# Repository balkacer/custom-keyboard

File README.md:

# Orange Moon Keyboard

This is a custom keyboard for the streamer [blodiemoon](https://www.twitch.tv/blodiemoon).

## Design

## Legends

## Plate Layout

## External links

- [Twitch](https://www.twitch.tv/blodiemoon)
- [Keyboard Layout Editor](http://www.keyboard-layout-editor.com/)
- [Auto Hotkey](https://www.autohotkey.com/)

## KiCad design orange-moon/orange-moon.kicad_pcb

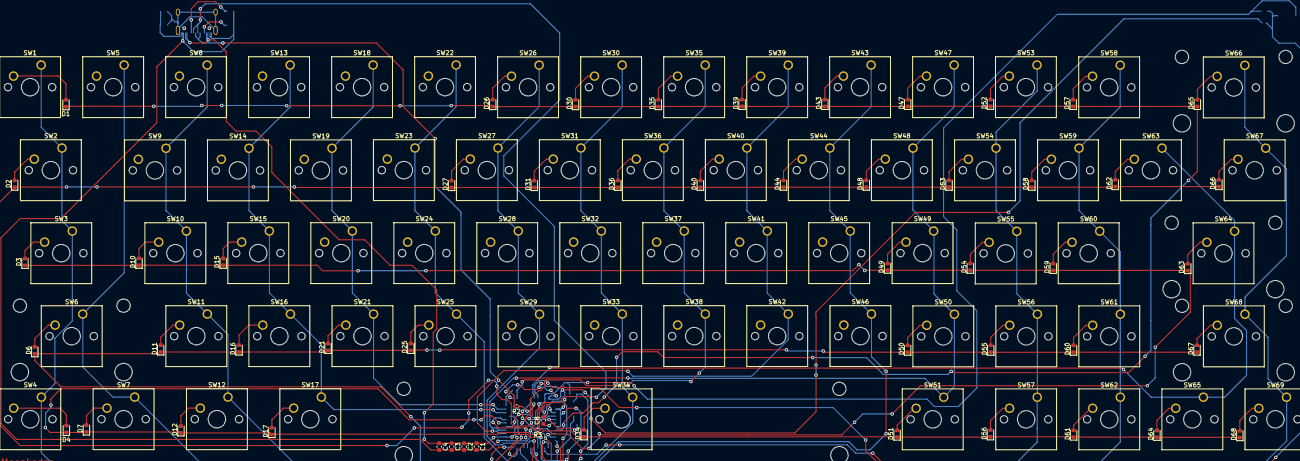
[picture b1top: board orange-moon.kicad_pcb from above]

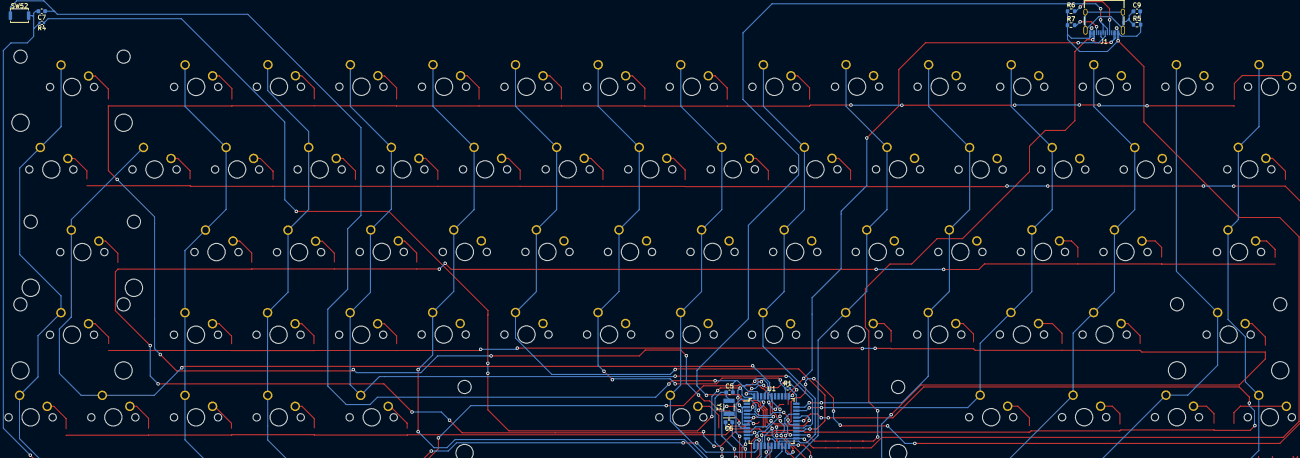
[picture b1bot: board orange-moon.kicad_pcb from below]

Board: 2 copper layers, 135 parts (13 on the bottom side), 82 nets.

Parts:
C1: 10u; C_0603_1608Metric
C2, C8: 1u; C_0603_1608Metric
C3, C4: 100u; C_0603_1608Metric
C5, C6: 22p; C_0603_1608Metric
C7, C9: 100n; C_0603_1608Metric
D1, D2, D3, D4, D6, D7, D10, D11, D12, D15, D16, D17, D21, D25, D26, D27, D30, D31, D34, D35, D36, D39, D40, D43, D44, D47, D48, D49, D50, D51, D52, D53, D54, D55, D56, D57, D58, D59, D60, D61, D62, D63, D64, D65, D66, D67, D68: D_Small; D_0603_1608Metric
J1: USB_C_Receptacle; USB_C_Receptacle_XKB_U262-16XN-4BVC11
R1, R4: 10k; R_0402_1005Metric
R2, R3: 22; R_0402_1005Metric
R5: 1M; R_0603_1608Metric
R6, R7: 5.1k; R_0603_1608Metric
SW1, SW4, SW5, SW8, SW9, SW10, SW11, SW12, SW13, SW14, SW15, SW16, SW18, SW19, SW20, SW21, SW22, SW23, SW24, SW25, SW26, SW27, SW28, SW29, SW30, SW31, SW32, SW33, SW35, SW36, SW37, SW38, SW39, SW40, SW41, SW42, SW43, SW44, SW45, SW46, SW47, SW48, SW49, SW50, SW53, SW54, SW55, SW56, SW57, SW58, SW59, SW60, SW61, SW62, SW63, SW65, SW69: Mechanical_Switch; SW_Cherry_MX_1.00u_PCB
SW2, SW67: Mechanical_Switch; SW_Cherry_MX_1.50u_PCB
SW3: Mechanical_Switch; SW_Cherry_MX_1.75u_PCB
SW6, SW66, SW68: Mechanical_Switch; SW_Cherry_MX_2.00u_PCB
SW7, SW17, SW51: Mechanical_Switch; SW_Cherry_MX_1.25u_PCB
SW34: Mechanical_Switch; SW_Cherry_MX_6.25u_PCB
SW52: SW_Push; SW_Push_SPST_NO_Alps_SKRK
SW64: Mechanical_Switch; SW_Cherry_MX_2.25u_PCB
U1: ATmega32U4-A; TQFP-44_10x10mm_P0.8mm
Y1: 16MHz; Resonator_SMD_Murata_CDSCB-2Pin_4.5x2.0mm

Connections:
+5V: C1.1, C2.1, C3.1, C4.1, J1.A4 (VBUS), J1.A9 (VBUS), J1.B4 (VBUS), J1.B9 (VBUS), R4.1, U1.2 (UVCC), U1.7 (VBUS), U1.14 (VCC), U1.24 (AVCC), U1.34 (VCC), U1.44 (AVCC)
COL1: SW1.1, SW2.1, SW3.1, SW4.1, U1.29 (PB5)
COL2: SW5.1, SW6.1, SW7.1, U1.30 (PB6)
COL3: SW8.1, SW9.1, SW10.1, SW11.1, SW12.1, U1.12 (PB7)
COL4: SW13.1, SW14.1, SW15.1, SW16.1, SW17.1, U1.31 (PC6)
COL5: SW18.1, SW19.1, SW20.1, SW21.1, U1.32 (PC7)
COL6: SW22.1, SW23.1, SW24.1, SW25.1, U1.18 (PD0)
COL7: SW26.1, SW27.1, SW28.1, SW29.1, U1.19 (PD1)
COL8: SW30.1, SW31.1, SW32.1, SW33.1, SW34.1, U1.20 (PD2)
COL9: SW35.1, SW36.1, SW37.1, SW38.1, U1.21 (PD3)
COL10: SW39.1, SW40.1, SW41.1, SW42.1, U1.25 (PD4)
COL11: SW43.1, SW44.1, SW45.1, SW46.1, U1.22 (PD5)
COL12: SW47.1, SW48.1, SW49.1, SW50.1, SW51.1, U1.26 (PD6)
COL13: SW53.1, SW54.1, SW55.1, SW56.1, SW57.1, U1.27 (PD7)
COL14: SW58.1, SW59.1, SW60.1, SW61.1, SW62.1, U1.41 (PF0)
COL15: SW63.1, SW64.1, SW65.1, U1.40 (PF1)
COL16: SW66.1, SW67.1, SW68.1, SW69.1, U1.39 (PF4)
GND: C1.2, C2.2, C3.2, C4.2, C5.2, C6.2, C7.1, C8.2, C9.2, J1.A1 (GND), J1.A12 (GND), J1.B1 (GND), J1.B12 (GND), R1.1, R5.2, R6.1, R7.1, SW52.1, U1.5 (UGND), U1.15 (GND), U1.23 (GND), U1.35 (GND), U1.43 (GND)
unnamed: C5.1, U1.17 (XTAL1), Y1.2
unnamed: C6.1, U1.16 (XTAL2), Y1.1
unnamed: C8.1, U1.6 (UCAP)
unnamed: C9.1, J1.S1 (SHIELD), R5.1
unnamed: D1.2 (A), SW1.2
unnamed: D2.2 (A), SW2.2
unnamed: D3.2 (A), SW3.2
unnamed: D4.2 (A), SW4.2
unnamed: D6.2 (A), SW6.2
unnamed: D7.2 (A), SW7.2
unnamed: D10.2 (A), SW10.2
unnamed: D11.2 (A), SW11.2
unnamed: D12.2 (A), SW12.2
unnamed: D15.2 (A), SW15.2
unnamed: D16.2 (A), SW16.2
unnamed: D21.2 (A), SW21.2
unnamed: D25.2 (A), SW25.2
unnamed: D27.2 (A), SW27.2
unnamed: D31.2 (A), SW31.2
unnamed: D34.2 (A), SW34.2
unnamed: D35.2 (A), SW35.2
unnamed: D36.2 (A), SW36.2
unnamed: D39.2 (A), SW39.2
unnamed: D40.2 (A), SW40.2
unnamed: D43.2 (A), SW43.2
unnamed: D49.2 (A), SW49.2
unnamed: D50.2 (A), SW50.2
unnamed: D51.2 (A), SW51.2
unnamed: D56.2 (A), SW57.2
unnamed: D57.2 (A), SW58.2
unnamed: D58.2 (A), SW59.2
unnamed: D59.2 (A), SW60.2
unnamed: D61.2 (A), SW62.2
unnamed: D62.2 (A), SW63.2
unnamed: D64.2 (A), SW65.2
unnamed: D65.2 (A), SW66.2
unnamed: D66.2 (A), SW67.2
unnamed: D67.2 (A), SW68.2
unnamed: R1.2, U1.33 (~HWB/PE2)
unnamed: R2.1, U1.4 (D+)
unnamed: R3.1, U1.3 (D-)
unnamed: J1.A5 (CC1), R6.2
unnamed: J1.B5 (CC2), R7.2
unnamed: D17.2 (A), SW17.2
unnamed: D26.2 (A), SW26.2
unnamed: D30.2 (A), SW30.2
unnamed: D44.2 (A), SW44.2
unnamed: D47.2 (A), SW47.2
unnamed: D48.2 (A), SW48.2
unnamed: D52.2 (A), SW53.2
unnamed: D53.2 (A), SW54.2
unnamed: D54.2 (A), SW55.2
unnamed: D55.2 (A), SW56.2
unnamed: D60.2 (A), SW61.2
unnamed: D63.2 (A), SW64.2
unnamed: D68.2 (A), SW69.2
ROW1: D1.1 (K), D26.1 (K), D30.1 (K), D35.1 (K), D39.1 (K), D43.1 (K), D47.1 (K), D52.1 (K), D57.1 (K), D65.1 (K), U1.8 (PB0)
ROW2: D2.1 (K), D27.1 (K), D31.1 (K), D36.1 (K), D40.1 (K), D44.1 (K), D48.1 (K), D53.1 (K), D58.1 (K), D62.1 (K), D66.1 (K), U1.9 (PB1)
ROW3: D3.1 (K), D10.1 (K), D15.1 (K), D49.1 (K), D54.1 (K), D59.1 (K), D63.1 (K), U1.10 (PB2)
ROW4: D6.1 (K), D11.1 (K), D16.1 (K), D21.1 (K), D25.1 (K), D50.1 (K), D55.1 (K), D60.1 (K), D67.1 (K), U1.11 (PB3)
ROW5: D4.1 (K), D7.1 (K), D12.1 (K), D17.1 (K), D34.1 (K), D51.1 (K), D56.1 (K), D61.1 (K), D64.1 (K), D68.1 (K), U1.28 (PB4)
RST: C7.2, R4.2, SW52.2, U1.13 (~RESET)
USB_DN: J1.A7 (D-), J1.B7 (D-), R3.2
USB_DP: J1.A6 (D+), J1.B6 (D+), R2.2

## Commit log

2022-02-19 Adding some changes
2022-02-19 Adding changes to legends
2022-02-25 KiCad project
2022-02-25 Upload plate layout
2022-02-25 Adding plate layout to readme
2022-02-25 Update KLE link
2022-02-25 Removing unnecessary info
2022-03-05 Adding new kicad project
